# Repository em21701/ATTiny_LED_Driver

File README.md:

ATTiny_LED_Driver
=================

LED Driver Board using and ATTiny processor for PWM and effects.

The goal of this project is to use the ATTiny as a Buck Driver for High Brightness LEDs. 
After getting a functional Buck Driver working I will add blink effects.

This driver board has 2 inputs and is intended for use as a turn signal/running light 
combo and brake light/running light combo for a motorcycle. As such the board has 2 inputs,
one for 12v power from the key and a second for 12v power from either the turn signal or 
brake light. The Key inuput will illuminate the LEDs to a low level and the second input 
will change the brightness to a significantly higher level.Blink effects will be added when 
used as a tail/brake combo to make the light more conspicuous. 

Currently planned blink effects are an invverted heartbeat and flash and fade. In the heart 
beat pattern the light will dim in a lub-dub pattern while brake light is illuminated. 
In the flash and fade pattern, the brake light will flash to full brightness then slowly fade
to a level brighter than running light level, but noticeably lower than full brightness. The
light will then flash back to full brightness and repeat.

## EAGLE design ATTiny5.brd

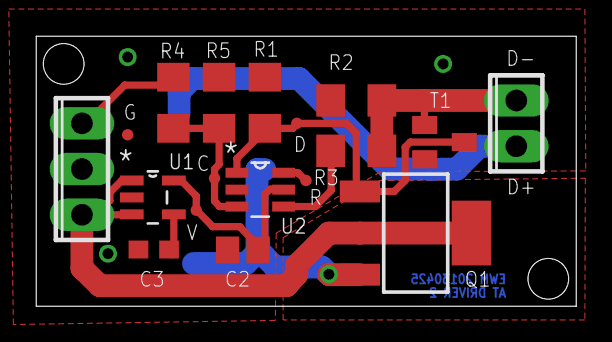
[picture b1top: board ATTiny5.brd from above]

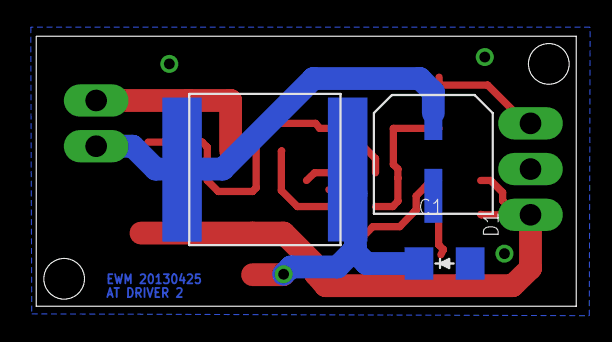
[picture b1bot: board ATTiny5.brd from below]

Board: 2 copper layers, 30.0 x 15.0 mm, 21 parts (3 on the bottom side), 12 nets.

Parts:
+5V: TPI; TPI_PAD
C1: 100u; CDE-AVE-X
C2: .1u; C0805
C3: 10n; C0603
D1: CD1206-B260; D1206
GND: TPI; TPI_PAD
L1: SRN8040
Q1: BSP100; SOT223
R1, R3: 10k; R1206
R2: 1; R1206
R4: 900; R1206
R5: 300; R1206
RESET: TPI; TPI_PAD
T1: BC846; SOT23
TPICLK: TPI; TPI_PAD
TPIDATA: TPI; TPI_PAD
U1: SPX5205M5-L-3-3; SOT95P280X145-5N
U2: ATTINY5-TSHR; SOT95P280X145-6N
X1: DIODES; 2POL254
X2: INPUT; 3POL254

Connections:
+14V: Q1.2, Q1.TAB, U1.1, U1.3, X2.1
BLINK: R4.1, R5.1, TPICLK.P$1, U2.3
D-: R2.2, R3.1, T1.1, X1.2
GND: C1.C-, C2.2, C3.2, D1.2, GND.P$1, R1.1, R2.1, R5.2, T1.2, U1.2, U2.2, X2.2
L+: D1.1, L1.P$1, Q1.3
MEASURE: R3.2, U2.4
MOSFET: Q1.1, R1.2, T1.3, TPIDATA.P$1, U2.1
unnamed: R4.2, X2.3
unnamed: C3.1, U1.4
unnamed: C1.C+, L1.P$2, X1.1
RESET: RESET.P$1, U2.6
VCC: +5V.P$1, C2.1, U1.5, U2.5

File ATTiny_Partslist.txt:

Partlist

Exported from ATTiny5.sch at 4/17/13 7:26 PM

EAGLE Version 6.4.0 Copyright (c) 1988-2013 CadSoft

Assembly variant: 

Part     Value           Device          Package          Library                    Sheet

C1       .1u             C-USC0805       C0805            resistor                   1
C2       .1u             C-USC0805       C0805            resistor                   1
D1       CD1206-B260     CD1206-B260     D1206            Personal                   1
L1       B82442H1104K    B82442H1104K    B82442H          Personal                   1
Q1       BSP100          BSP100          SOT223           Personal                   1
R1       10k             R-US_R1206      R1206            resistor                   1
R2       .1              R-US_R1206      R1206            resistor                   1
R3       10k             R-US_R1206      R1206            resistor                   1
R4       900             R-US_R1206      R1206            resistor                   1
R5       300             R-US_R1206      R1206            resistor                   1
U1       SPX5205M5-L-3-3 SPX5205M5-L-3-3 SOT95P280X145-5N Exar_By_element14_Batch_1  1
U2       ATTINY5-TSHR    ATTINY5-TSHR    SOT95P280X145-6N Atmel_By_element14_Batch_1 1
X1       DIODES          MPT2            2POL254          con-phoenix-254            1
X2                       MPT3            3POL254          con-phoenix-254            1

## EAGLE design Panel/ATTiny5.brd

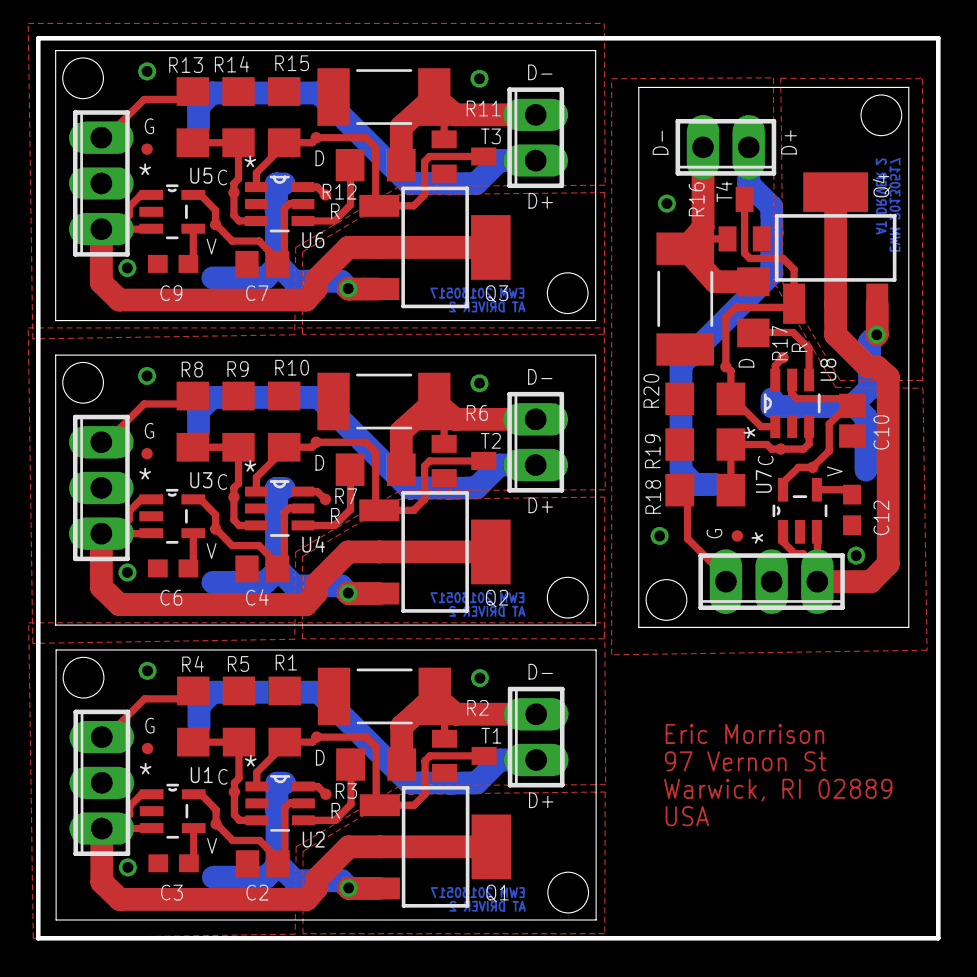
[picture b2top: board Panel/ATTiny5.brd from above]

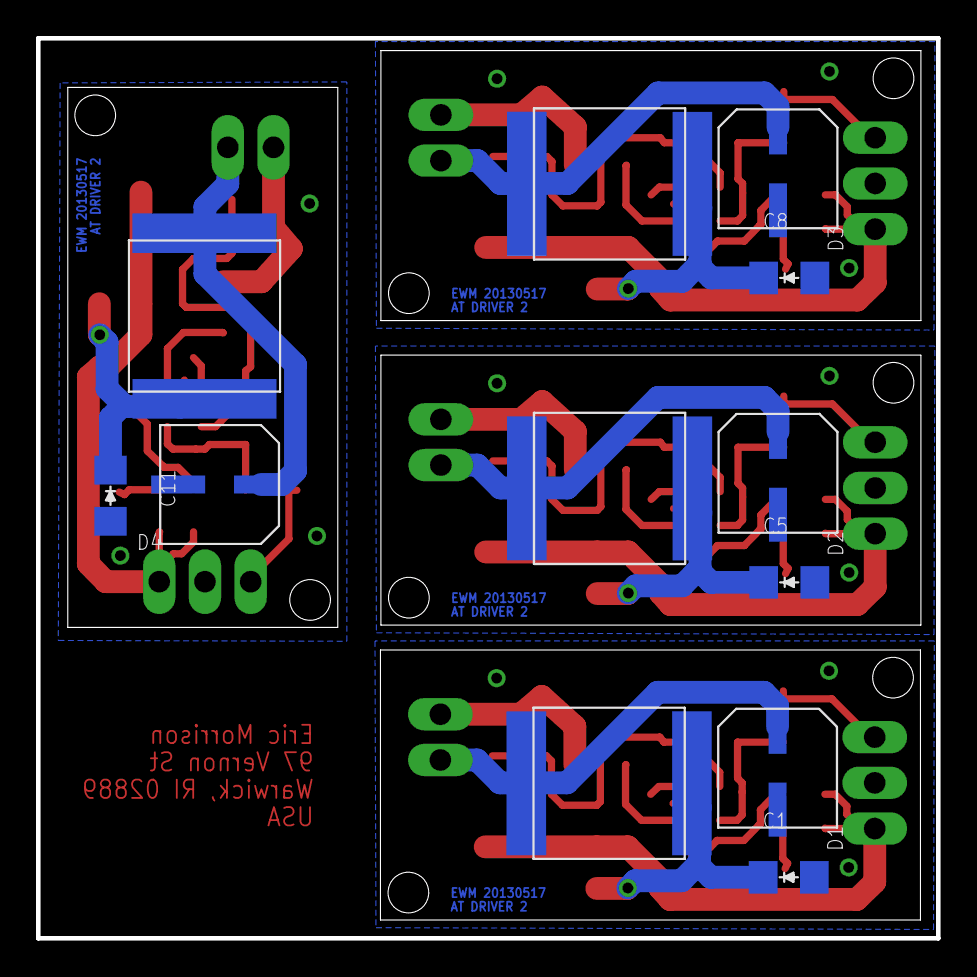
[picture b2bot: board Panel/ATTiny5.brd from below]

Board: 2 copper layers, 50.0 x 50.0 mm, 84 parts (12 on the bottom side), 48 nets.

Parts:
+5V, +5V1, +5V2, +5V3: TPI; TPI_PAD
C1, C5, C8, C11: 100u; CDE-AVE-X
C2, C4, C7, C10: .1u; C0805
C3, C6, C9, C12: 10n; C0603
D1, D2, D3, D4: CD1206-B260; D1206
GND, GND1, GND2, GND3: TPI; TPI_PAD
L1, L2, L3, L4: SRN8040
Q1, Q2, Q3, Q4: BSP100; SOT223
R1, R3, R7, R10, R12, R15, R17, R20: 10k; R1206
R2, R6, R11, R16: 1; R2512
R4, R8, R13, R18: 910; R1206
R5, R9, R14, R19: 300; R1206
RESET, RESET1, RESET2, RESET3: TPI; TPI_PAD
T1, T2, T3, T4: BC846; SOT23
TPICLK, TPICLK1, TPICLK2, TPICLK3: TPI; TPI_PAD
TPIDATA, TPIDATA1, TPIDATA2, TPIDATA3: TPI; TPI_PAD
U1, U3, U5, U7: SPX5205M5-L-3-3; SOT95P280X145-5N
U2, U4, U6, U8: ATTINY5-TSHR; SOT95P280X145-6N
X1, X4, X6, X8: DIODES; 2POL254
X2, X3, X5, X7: INPUT; 3POL254

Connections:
+14V: Q1.2, Q1.TAB, U1.1, U1.3, X2.1
+14V1: Q2.2, Q2.TAB, U3.1, U3.3, X3.1
+14V2: Q3.2, Q3.TAB, U5.1, U5.3, X5.1
+14V3: Q4.2, Q4.TAB, U7.1, U7.3, X7.1
BLINK: R4.1, R5.1, TPICLK.P$1, U2.3
BLINK1: R8.1, R9.1, TPICLK1.P$1, U4.3
BLINK2: R13.1, R14.1, TPICLK2.P$1, U6.3
BLINK3: R18.1, R19.1, TPICLK3.P$1, U8.3
D-: R2.2, R3.1, T1.1, X1.2
D-1: R6.2, R7.1, T2.1, X4.2
D-2: R11.2, R12.1, T3.1, X6.2
D-3: R16.2, R17.1, T4.1, X8.2
GND: C1.C-, C2.2, C3.2, D1.2, GND.P$1, R1.1, R2.1, R5.2, T1.2, U1.2, U2.2, X2.2
GND1: C4.2, C5.C-, C6.2, D2.2, GND1.P$1, R6.1, R9.2, R10.1, T2.2, U3.2, U4.2, X3.2
GND2: C7.2, C8.C-, C9.2, D3.2, GND2.P$1, R11.1, R14.2, R15.1, T3.2, U5.2, U6.2, X5.2
GND3: C10.2, C11.C-, C12.2, D4.2, GND3.P$1, R16.1, R19.2, R20.1, T4.2, U7.2, U8.2, X7.2
L+: D1.1, L1.P$1, Q1.3
L+1: D2.1, L2.P$1, Q2.3
L+2: D3.1, L3.P$1, Q3.3
L+3: D4.1, L4.P$1, Q4.3
MEASURE: R3.2, U2.4
MEASURE1: R7.2, U4.4
MEASURE2: R12.2, U6.4
MEASURE3: R17.2, U8.4
MOSFET: Q1.1, R1.2, T1.3, TPIDATA.P$1, U2.1
MOSFET1: Q2.1, R10.2, T2.3, TPIDATA1.P$1, U4.1
MOSFET2: Q3.1, R15.2, T3.3, TPIDATA2.P$1, U6.1
MOSFET3: Q4.1, R20.2, T4.3, TPIDATA3.P$1, U8.1
unnamed: R4.2, X2.3
unnamed: C3.1, U1.4
unnamed: C1.C+, L1.P$2, X1.1
unnamed: C5.C+, L2.P$2, X4.1
unnamed: R8.2, X3.3
unnamed: C6.1, U3.4
unnamed: C8.C+, L3.P$2, X6.1
unnamed: R13.2, X5.3
unnamed: C9.1, U5.4
unnamed: C11.C+, L4.P$2, X8.1
unnamed: R18.2, X7.3
unnamed: C12.1, U7.4
RESET: RESET.P$1, U2.6
RESET1: RESET1.P$1, U4.6
RESET2: RESET2.P$1, U6.6
RESET3: RESET3.P$1, U8.6
VCC: +5V.P$1, C2.1, U1.5, U2.5
VCC1: +5V1.P$1, C4.1, U3.5, U4.5
VCC2: +5V2.P$1, C7.1, U5.5, U6.5
VCC3: +5V3.P$1, C10.1, U7.5, U8.5

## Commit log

2013-04-28 inital git version
2013-04-29 Added Code and Panel dirs. Updated Flowchart
2013-04-29 Flow Chart change
    Flow chart changed from: PWM = Gain*Error to: PWM += Gain*Error
2013-04-29 Added ToDo
2013-04-30 Added reference file Using Avr Counter.pdf
2013-04-30 Added programming hardware directory
    Includes solidworks files for the board, programming fixture, and a txt
    file with wiring color code.
2013-05-01 Edited Readme file
2013-05-14 Updated Board
    Updated Board with Optional current limiting transistor and properly
    sized and connected output cap.
2013-05-17 Component Change, New Panel, New BOM
    Changed the size of R2 for more cost effective 1W resistor. Added
    Digikey Part Num and pricing to each part and used export BOM to create
    better part list. Created New 5cm x 5cm SEEED panel from modified board.
    Created Updated Gerbers.
